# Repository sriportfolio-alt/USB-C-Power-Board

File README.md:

# USB-C 5V Power Supply Board

A compact USB Type-C power input board designed to provide a regulated 5V supply for embedded systems and development projects.

This project demonstrates USB-C power sink implementation, PCB design best practices, power protection circuitry, and hardware documentation using KiCad.

---

## Features

- USB Type-C power input
- USB-C sink implementation using CC pull-down resistors
- 5V output
- Resettable Polyfuse for over-current protection
- TVS diode for ESD protection
- Power status LED
- Test points for debugging
- 2-layer PCB
- Designed using KiCad

---

## Applications

- ESP32 Projects
- STM32 Development
- IoT Devices
- Embedded Systems
- Robotics
- Sensor Nodes
- Portable Electronics

---

## Specifications

| Parameter | Value |
|------------|---------|
| Input Connector | USB Type-C |
| Input Voltage | 5V |
| Output Voltage | 5V |
| Maximum Current | 1A |
| PCB Layers | 2 |
| PCB Thickness | 1.6 mm |

---

## Hardware Overview

USB-C Connector
↓
Polyfuse
↓
TVS Protection
↓
5V Output
↓
Power LED

CC1 and CC2 are connected to ground through 5.1kΩ pull-down resistors to identify the board as a USB-C power sink.

---

## Bill of Materials

| Component | Description |
|------------|-------------|
| USB-C Connector | USB Type-C Receptacle |
| Polyfuse | 1A Resettable Fuse |
| TVS Diode | USB ESD Protection |
| 330Ω | LED Current Limiting |
| 5.1kΩ ×2 | USB-C CC Pull-down |
| 10µF Capacitor | Input Filtering |
| 100nF Capacitor | Decoupling |

---

## Design Considerations

- USB Type-C implemented according to USB-C sink requirements.
- 5.1kΩ pull-down resistors used on CC1 and CC2.
- Polyfuse protects against excessive current.
- TVS diode provides ESD protection.
- Short power paths minimize voltage drop.
- Continuous ground plane improves EMC and reduces noise.

---

## Software

- KiCad 9
- Interactive Router
- 3D Viewer

---

## Future Improvements

- USB Power Delivery (PD) Support
- 3.3V LDO Output
- Current Measurement
- Reverse Polarity Protection
- Buck Converter
- USB Data Support
- Output Protection IC

---

## Learning Outcomes

This project demonstrates:

- USB Type-C Fundamentals
- PCB Design
- Schematic Capture
- Power Supply Design
- ESD Protection
- PCB Layout
- Manufacturing File Generation
- Design for Manufacturing (DFM)

---

## Author

**Sriram**

Embedded Systems | PCB Design | IoT | STM32 | ESP32

GitHub: https://github.com/sriportfolio-alt

LinkedIn: www.linkedin.com/in/sriram-ganesan-a1a171226

---

## License

This project is licensed under the MIT License.

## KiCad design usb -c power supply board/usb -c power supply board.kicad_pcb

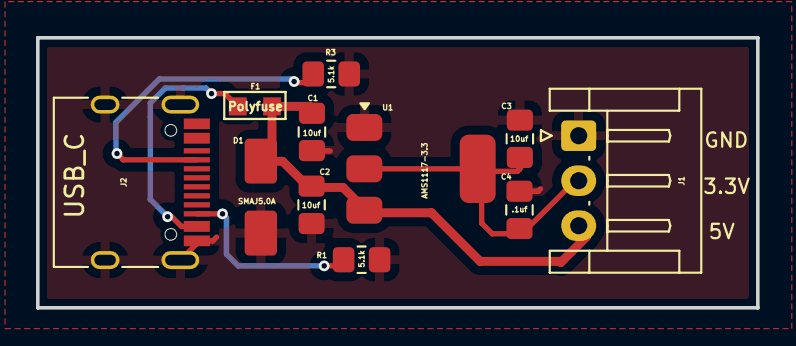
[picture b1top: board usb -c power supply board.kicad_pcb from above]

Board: 2 copper layers, 40.0 x 15.0 mm, 11 parts (0 on the bottom side), 6 nets.

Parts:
C1, C2, C3: 10uf; C_0805_2012Metric_Pad1.18x1.45mm_HandSolder
C4: .1uf; C_0805_2012Metric_Pad1.18x1.45mm_HandSolder
D1: SMAJ5.0A; D_SMA
F1: Polyfuse; 0603-F1608X100N
J1: output; JST_EH_S3B-EH_1x03_P2.50mm_Horizontal
J2: USB_C; USB_C_Receptacle_HRO_TYPE-C-31-M-12
R1, R3: 5.1k; R_0805_2012Metric_Pad1.20x1.40mm_HandSolder
U1: AMS1117-3.3; SOT-223-3_TabPin2

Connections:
3.3V: C3.1, C4.1, J1.2, U1.2 (VO)
5V: C1.1, C2.1, D1.1 (A1), F1.2, J1.3, U1.3 (VI)
GND: C1.2, C2.2, C3.2, C4.2, D1.2 (A2), J1.1, J2.A12 (GND), J2.S1 (SHIELD), R1.2, R3.2, U1.1 (GND)
unnamed: F1.1, J2.A9 (VBUS)
unnamed: J2.A5 (CC1), R3.1
unnamed: J2.B5 (CC2), R1.1
